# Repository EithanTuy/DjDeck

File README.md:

The pcb files for my custom dj deck

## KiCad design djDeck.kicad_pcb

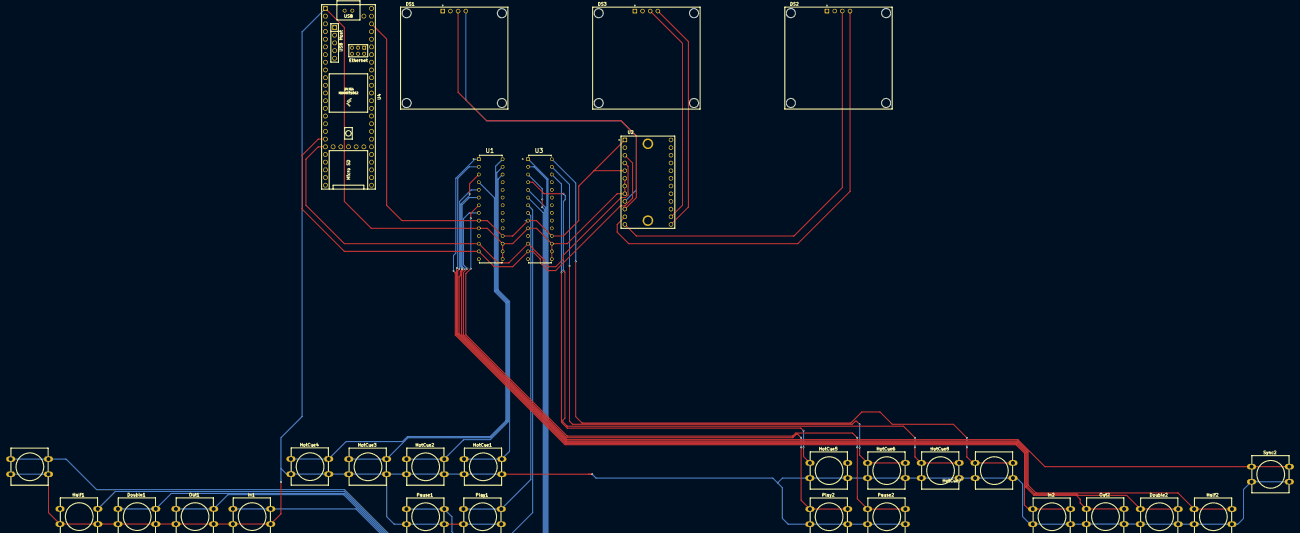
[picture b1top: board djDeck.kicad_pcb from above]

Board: 2 copper layers, 29 parts (0 on the bottom side), 32 nets.

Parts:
DS1, DS2, DS3: OLED_128X64_1.3_I2C; LCD_OLED_128X64_1.3_I2C
Double1, Double2: SW_SPST; SW_PUSH-12mm
Half1, Half2: SW_SPST; SW_PUSH-12mm
HotCue1, HotCue2, HotCue3, HotCue4, HotCue5, HotCue6, HotCue7, HotCue8: SW_SPST; SW_PUSH-12mm
In1, In2: SW_SPST; SW_PUSH-12mm
Out1, Out2: SW_SPST; SW_PUSH-12mm
Pause1, Pause2: SW_SPST; SW_PUSH-12mm
Play1, Play2: SW_SPST; SW_PUSH-12mm
Sync1, Sync2: SW_SPST; SW_PUSH-12mm
U1, U3: MCP23017-E_SP; DIP787W45P254L3556H508Q28
U2: 2717; MODULE_2717
U4: Teensy4.1; Teensy41

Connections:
unnamed: DS1.3 (SCK), U2.10 (SCL0)
unnamed: DS1.4 (SDA), U2.9 (SDA0)
unnamed: DS2.3 (SCK), U2.12 (SCL1)
unnamed: DS2.4 (SDA), U2.11 (SDA1)
unnamed: DS3.3 (SCK), U2.14 (SCL2)
unnamed: DS3.4 (SDA), U2.13 (SDA2)
unnamed: Double1.1 (A), U3.5 (GPB4)
unnamed: Double1.2 (B), Double2.2 (B), Half1.2 (B), Half2.2 (B), HotCue1.2 (B), HotCue2.2 (B), HotCue3.2 (B), HotCue4.2 (B), HotCue5.2 (B), HotCue6.2 (B), HotCue7.2 (B), HotCue8.2 (B), In1.2 (B), In2.2 (B), Out1.2 (B), Out2.2 (B), Pause1.2 (B), Pause2.2 (B), Play1.2 (B), Play2.2 (B), Sync1.2 (B), Sync2.2 (B), U1.10 (VSS), U1.15 (A0), U1.16 (A1), U1.17 (A2), U2.6 (A0), U2.7 (A1), U2.8 (A2), U3.10 (VSS), U3.15 (A0), U3.16 (A1), U3.17 (A2), U4.1 (GND)
unnamed: Double2.1 (A), U1.5 (GPB4)
unnamed: Half1.1 (A), U3.3 (GPB2)
unnamed: Half2.1 (A), U1.3 (GPB2)
unnamed: HotCue1.1 (A), U1.26 (GPA5)
unnamed: HotCue2.1 (A), U1.27 (GPA6)
unnamed: HotCue3.1 (A), U1.28 (GPA7)
unnamed: HotCue4.1 (A), U1.4 (GPB3)
unnamed: HotCue5.1 (A), U3.26 (GPA5)
unnamed: HotCue6.1 (A), U3.27 (GPA6)
unnamed: HotCue7.1 (A), U3.28 (GPA7)
unnamed: HotCue8.1 (A), U3.4 (GPB3)
unnamed: In1.1 (A), U3.1 (GPB0)
unnamed: In2.1 (A), U1.1 (GPB0)
unnamed: Out1.1 (A), U3.2 (GPB1)
unnamed: Out2.1 (A), U1.2 (GPB1)
unnamed: Pause1.1 (A), U3.7 (GPB6)
unnamed: Pause2.1 (A), U1.7 (GPB6)
unnamed: Play1.1 (A), U3.8 (GPB7)
unnamed: Play2.1 (A), U1.8 (GPB7)
unnamed: Sync1.1 (A), U3.6 (GPB5)
unnamed: Sync2.1 (A), U1.6 (GPB5)
unnamed: U1.12 (SCK), U2.4 (SCL), U3.12 (SCK), U4.19 (27_A13_SCK1)
unnamed: U1.13 (SDA), U2.3 (SDA), U3.13 (SDA), U4.18 (26_A12_MOSI1)
unnamed: U1.9 (VDD), U1.18 (~RESET), U2.1 (VIN), U2.5 (RST), U3.9 (VDD), U3.18 (~RESET), U4.46 (3V3)
